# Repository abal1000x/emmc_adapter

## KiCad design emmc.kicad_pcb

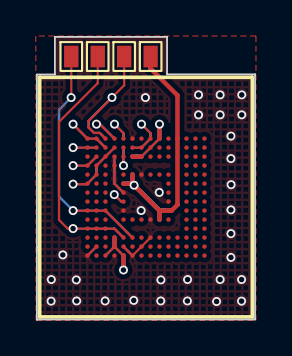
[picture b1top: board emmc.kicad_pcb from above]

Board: 2 copper layers, 12.1 x 15.7 mm, 6 parts (1 on the bottom side), 15 nets.

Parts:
Bottom1: Bottom
SP1: CMD
SP2: CLK
SP3: DAT0
SP4: VDDF
Top1: Top

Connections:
GND: Bottom1.A6 (VSS), Bottom1.C4 (VSS), Bottom1.E7 (VSS), Bottom1.G5 (VSS), Bottom1.H10 (VSS), Bottom1.J5 (VSS), Bottom1.K8 (VSS), Bottom1.N2 (VSS), Bottom1.N5 (VSS), Bottom1.P4 (VSS), Bottom1.P6 (VSS), Top1.A6 (VSS), Top1.C4 (VSS), Top1.E7 (VSS), Top1.G5 (VSS), Top1.H10 (VSS), Top1.J5 (VSS), Top1.K8 (VSS), Top1.N2 (VSS), Top1.N5 (VSS), Top1.P4 (VSS), Top1.P6 (VSS)
unnamed: Bottom1.M6 (CLK), SP2.CLK, Top1.M6 (CLK)
unnamed: Bottom1.M5 (CMD), SP1.CMD, Top1.M5 (CMD)
unnamed: Bottom1.A3 (DAT0), SP3.DAT0, Top1.A3 (DAT0)
unnamed: Bottom1.A4 (DAT1), Top1.A4 (DAT1)
unnamed: Bottom1.A5 (DAT2), Top1.A5 (DAT2)
unnamed: Bottom1.B2 (DAT3), Top1.B2 (DAT3)
unnamed: Bottom1.B3 (DAT4), Top1.B3 (DAT4)
unnamed: Bottom1.B4 (DAT5), Top1.B4 (DAT5)
unnamed: Bottom1.B5 (DAT6), Top1.B5 (DAT6)
unnamed: Bottom1.B6 (DAT7), Top1.B6 (DAT7)
unnamed: Bottom1.H5 (DS), Top1.H5 (DS)
VDD: Bottom1.C6 (VDD), Bottom1.M4 (VDD), Bottom1.N4 (VDD), Bottom1.P3 (VDD), Bottom1.P5 (VDD), Top1.C6 (VDD), Top1.M4 (VDD), Top1.N4 (VDD), Top1.P3 (VDD), Top1.P5 (VDD)
VDDF: Bottom1.E6 (VDDF), Bottom1.F5 (VDDF), Bottom1.J10 (VDDF), Bottom1.K9 (VDDF), SP4.VDDF, Top1.E6 (VDDF), Top1.F5 (VDDF), Top1.J10 (VDDF), Top1.K9 (VDDF)
VDDI: Bottom1.C2 (VDDI), Top1.C2 (VDDI)

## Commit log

2023-07-18 Initial Files
2023-08-13 Revision: * Change background plane to hatched mode. This is hopefully could reduce the 'bending' pcb, when heated. * All pin will be shown. Hopefully it will make the 'orientation alignment' worked.
